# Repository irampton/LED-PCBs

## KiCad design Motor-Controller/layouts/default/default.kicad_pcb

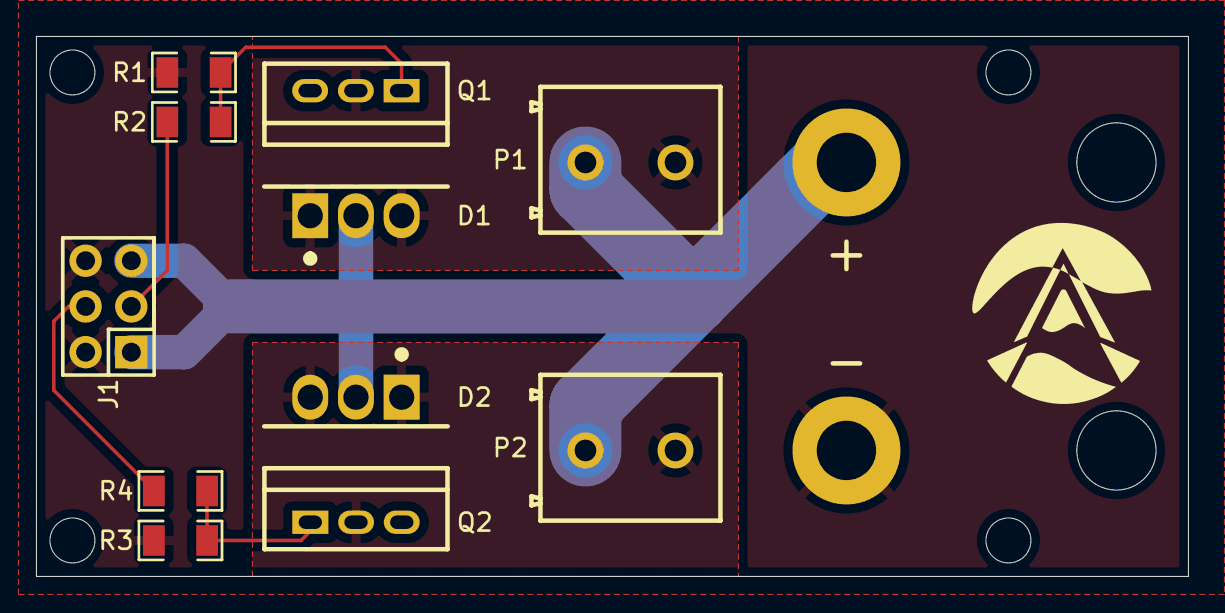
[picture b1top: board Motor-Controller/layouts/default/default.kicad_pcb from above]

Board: 2 copper layers, 64.0 x 30.0 mm, 13 parts (0 on the bottom side), 8 nets.

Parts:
+: M18_10AWG_PAD
-: M18_10AWG_PAD
D1, D2: TO-220AB-3_L10.4-W4.6-P2.54-T
J1: HDR-TH_6P-P2.54-V-M-R2-C3-S2.54-1
P1, P2: CONN-TH_2P-P5.00_CPC3703CTR
Q1, Q2: TO-220AB-3_L10.3-W4.5-P2.54-L-1
R1, R3: 10kΩ ±1%; R1206
R2, R4: 330Ω ±5%; R1206

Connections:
GATE1: Q1.1, R1.1, R2.2
GATE2: Q2.1, R3.1, R4.2
MOTOR1: D1.1, D1.3, P1.2, Q1.2
MOTOR2: D2.1, D2.3, P2.2, Q2.2
PWM1: J1.3, R2.1
PWM2: J1.4, R4.1
hv: +.1, D1.2, D2.2, J1.1, J1.5, P1.1, P2.1
lv: -.1, J1.2, J1.6, Q1.3, Q2.3, R1.2, R3.2

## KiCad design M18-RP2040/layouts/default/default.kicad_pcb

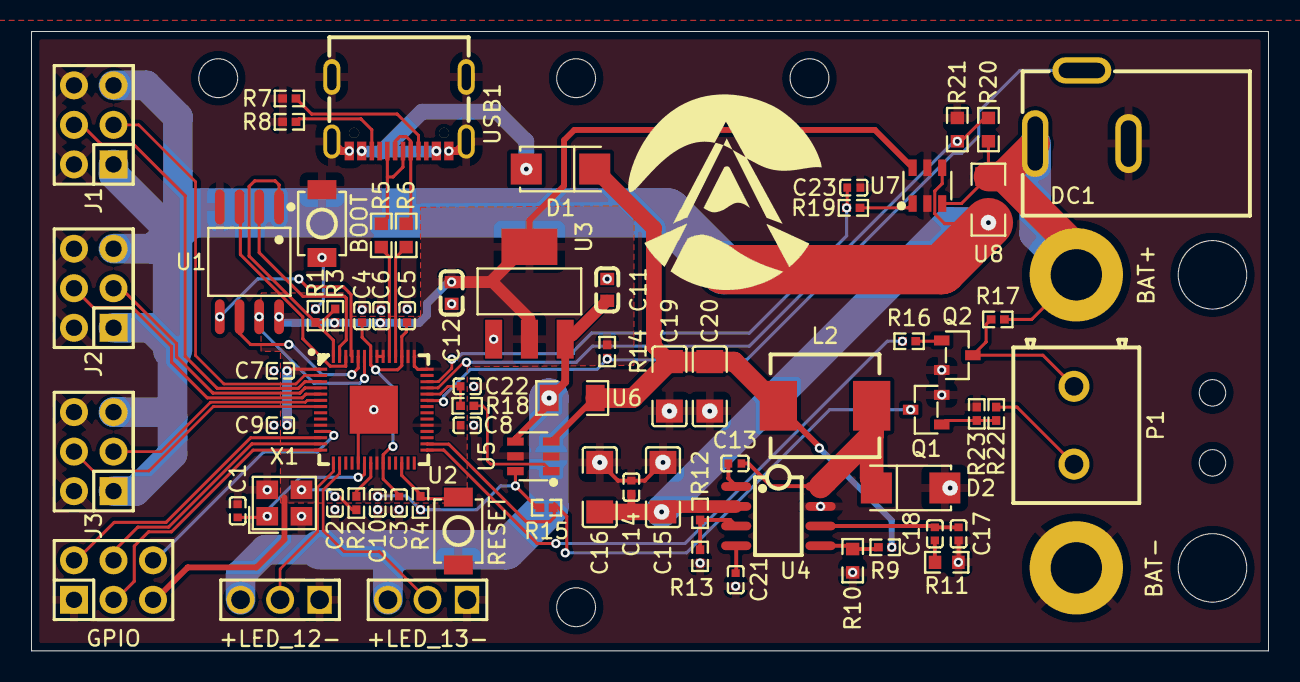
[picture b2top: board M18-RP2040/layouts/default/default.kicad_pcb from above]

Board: 2 copper layers, 79.5 x 39.8 mm, 73 parts (0 on the bottom side), 56 nets.

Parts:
+LED_12-, +LED_13-: HDR-TH_3P-P2.54-V-M-1
BAT+: M18_10AWG_PAD
BAT-: M18_10AWG_PAD
BOOT: SW-SMD_L3.9-W3.0-P4.45
C1, C2: 22pF ±5%; C0402
C3, C4, C5, C6, C7, C8, C9, C10: 1µF ±10%; C0402
C11: 10µF ±10%; C0603
C12: 22µF ±20%; C0603
C13: 100nF ±10%; C0402
C14, C21, C22, C23: 10nF ±10%; C0402
C15, C16: 4.7µF ±10%; C1206
C17: 47pF ±5%; C0402
C18: 1nF ±10%; C0402
C19, C20: 47µF ±20%; C1206
D1: SMA_L4.3-W2.6-LS5.2-RD
D2: Vf {ℝ+}V; SMA_L4.3-W2.6-LS5.2-RD
DC1: DC-IN-TH_PJ-002BH
GPIO: HDR-TH_6P-P2.54-V-M-R2-C3-S2.54-1
J1, J2, J3: HDR-TH_6P-P2.54-V-M-R2-C3-S2.54-1
L2: L 6.8µH ±20%; IND-SMD_L7.0-W6.6
P1: CONN-TH_2P-P5.00_CPC3703CTR
Q1, Q2: SOT-23-3_L2.9-W1.3-P1.90-LS2.4-BR
R1, R2: 1kΩ ±1%; R0402
R3, R4, R9, R14, R15, R17, R22, R23: 10kΩ ±1%; R0402
R5, R6: 22Ω ±1%; R0603
R7, R8: 5.1kΩ ±1%; R0402
R10: 1.8kΩ ±1%; R0603
R11: 30kΩ ±1%; R0603
R12: 330kΩ ±1%; R0402
R13: 68kΩ ±1%; R0402
R16: 330Ω ±1%; R0402
R18, R19: 220Ω ±1%; R0402
R20: 150kΩ ±1%; R0603
R21: 22kΩ ±1%; R0603
RESET: SW-SMD_L3.9-W3.0-P4.45
U1: SOIC-8_L5.3-W5.3-P1.27-LS8.0-BL
U2: LQFN-56_L7.0-W7.0-P0.4-EP
U3: SOT-223-3_L6.5-W3.4-P2.30-LS7.0-BR
U4: SOIC-8_L5.0-W4.0-P1.27-LS6.0-BL
U5, U7: SOT-23-6_L2.9-W1.6-P0.95-LS2.8-BL
U6, U8: R1206
USB1: USB-C_UC09-0B16F00P11
X1: CRYSTAL-SMD_4P-L3.2-W2.5-BL

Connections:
1V1: C3.1, C4.1, C5.1, U2.23, U2.45, U2.50
3: DC1.3, R14.1, U2.37
3V3: C6.1, C7.1, C8.1, C9.1, C10.1, C12.1, GPIO.5, R3.1, R4.1, R14.2, R15.1, U1.8, U2.1, U2.10, U2.22, U2.33, U2.42, U2.43, U2.44, U2.48, U2.49, U3.2, U3.4, U5.6, U7.6
5V: +LED_12-.3, +LED_13-.3, C11.1, U3.3, U5.4, U6.2
5Vin: C19.1, C20.1, D1.1, L2.2, R9.1, U5.3, U6.1
CC1: R7.1, USB1.A5
CC2: R8.1, USB1.B5
D: Q1.3, R15.2, U2.30
DATA_N: R6.1, USB1.A7, USB1.B7
DATA_P: R5.1, USB1.A6, USB1.B6
DC: P1.2, R22.1
DP: P1.1, Q2.3, R17.2
EN: R12.2, R13.1, U4.3
G: Q1.1, R22.2, R23.1
G-1: Q2.1, R16.1
GND: +LED_12-.1, +LED_13-.1, BAT-.1, BOOT.1, C1.2, C2.2, C3.2, C4.2, C5.2, C6.2, C7.2, C8.2, C9.2, C10.2, C11.2, C12.2, C14.2, C15.2, C16.2, C17.2, C19.2, C20.2, C21.2, C22.2, C23.2, D2.2, DC1.2, GPIO.1, J1.2, J1.6, J2.2, J2.6, J3.2, J3.6, Q1.2, Q2.2, R7.2, R8.2, R10.2, R11.2, R13.2, R21.2, R23.2, RESET.1, U1.4, U2.19, U2.57, U3.1, U4.7, U5.2, U5.5, U7.2, U7.5, USB1.17, USB1.18, USB1.19, USB1.20, USB1.A1B12, USB1.B1A12, X1.2, X1.4
GPIO0: J1.3, U2.2
GPIO1: J1.4, U2.3
GPIO2: J2.3, U2.4
GPIO3: J2.4, U2.5
GPIO4: J3.3, U2.6
GPIO5: J3.4, U2.7
GPIO12: +LED_12-.2, U2.15
GPIO13: +LED_13-.2, U2.16
MISO: GPIO.6, U2.11
MOSI: GPIO.3, U2.14
OUT: R18.1, U5.1
OUT-1: R19.1, U7.1
RUN: R4.2, RESET.2, U2.26
SCLK: GPIO.4, U2.13
USB_DM: R6.2, U2.46
USB_DP: R5.2, U2.47
V+: C14.1, C15.1, C16.1, J1.1, J1.5, J2.1, J2.5, J3.1, J3.5, R12.1, U4.2, U7.4, U8.2
VIN: BAT+.1, DC1.1, R17.1, R20.1, U7.3, U8.1
VSENSE: R9.2, R10.1, U4.5
XOUT: R2.1, U2.21
boot_cap-power-hv: C13.1, U4.1
c_osc_1-power-hv: C1.1, U2.20, X1.1
c_osc_2-power-hv: C2.1, R2.2, X1.3
cathode: C13.2, D2.1, L2.1, U4.8
comp_c2-power-hv: C17.1, C18.1, U4.6
cs: R1.2, R3.2, U1.1, U2.56
gpio18: R16.2, U2.29
gpio27_a1: R20.2, R21.1, U2.39
hv: C22.1, R18.2, U2.38
io0: U1.5, U2.53
io1: U1.2, U2.55
io2: U1.3, U2.54
io3: U1.7, U2.51
lv: C18.2, R11.1
output: BOOT.2, R1.1
sclk: U1.6, U2.52
spi_cs: GPIO.2, U2.12
ss_cap-power-hv: C21.1, U4.4
vUSB: D1.2, USB1.A4B9, USB1.B4A9
vin_sense_c1-power-hv: C23.1, R19.2, U2.40

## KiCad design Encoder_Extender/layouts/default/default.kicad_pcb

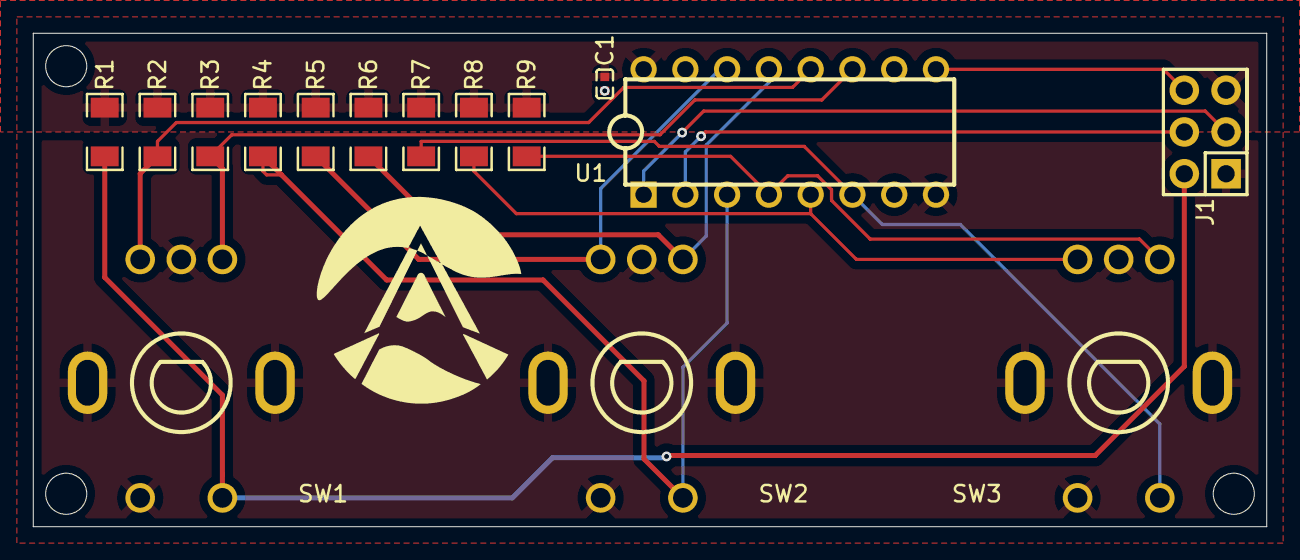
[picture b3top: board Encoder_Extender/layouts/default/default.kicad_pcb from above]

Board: 2 copper layers, 75.0 x 30.0 mm, 16 parts (1 on the bottom side), 14 nets.

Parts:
C1: 100nF ±10%; C0402
J1: HDR-TH_6P-P2.54-V-M-R2-C3-S2.54-1
QR*****: LED-GitHub-QR-MD
R1, R2, R3, R4, R5, R6, R7, R8, R9: 10kΩ ±1%; R1206
SW1, SW2, SW3: SW-TH_5P-L12.5-W13.4-P2.50-LS14.5
U1: DIP-16_L19.8-W6.5-P2.54-LS7.6-BL

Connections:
3V3: C1.1, J1.5, R1.1, R2.1, R3.1, R4.1, R5.1, R6.1, R7.1, R8.1, R9.1, U1.16
A: R3.2, SW1.1, U1.11
A-1: R6.2, SW2.1, U1.13
A-2: R9.2, SW3.1, U1.4
B: R2.2, SW1.3, U1.12
B-1: R5.2, SW2.3, U1.14
B-2: R8.2, SW3.3, U1.5
CLOCK: J1.4, U1.2
CS: J1.2, R1.2, SW1.4
E: R4.2, SW2.4, U1.3
GND: C1.2, J1.1, SW1.2, SW1.5, SW1.7, SW1.8, SW2.2, SW2.5, SW2.7, SW2.8, SW3.2, SW3.5, SW3.7, SW3.8, U1.8, U1.10, U1.15
H: R7.2, SW3.4, U1.6
RX: J1.6, U1.9
TX: J1.3, U1.1

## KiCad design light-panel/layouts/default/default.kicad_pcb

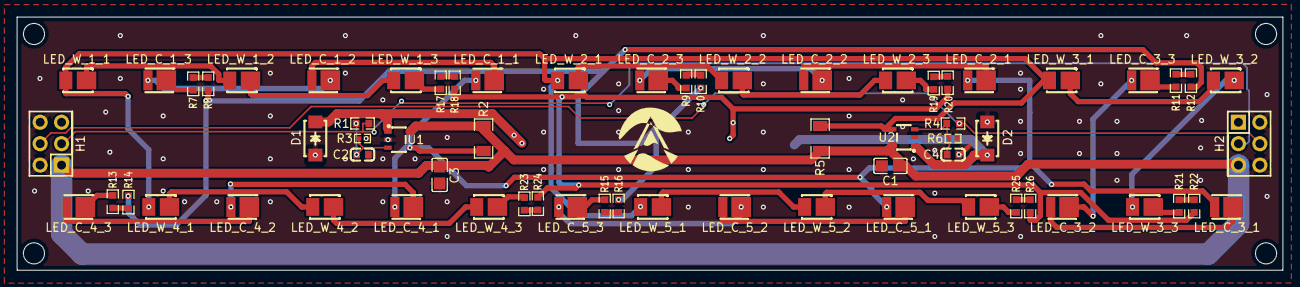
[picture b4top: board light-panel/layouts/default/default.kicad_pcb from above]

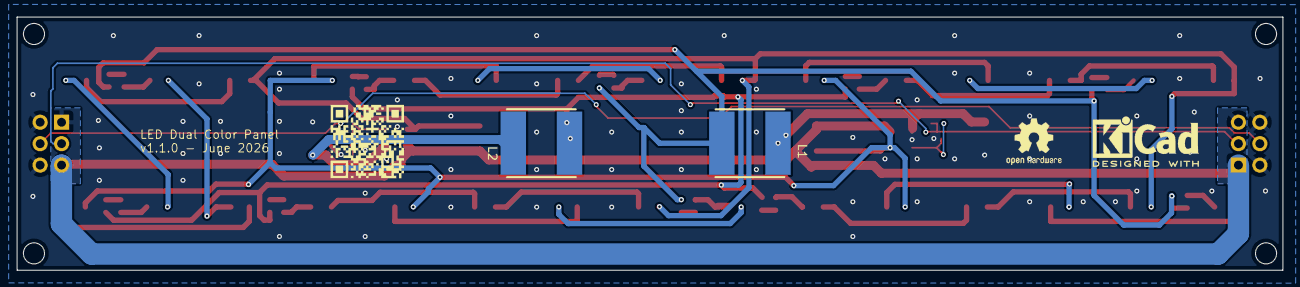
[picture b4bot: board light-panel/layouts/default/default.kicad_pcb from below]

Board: 2 copper layers, 150.0 x 30.0 mm, 69 parts (3 on the bottom side), 52 nets.

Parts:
C1, C3: 10µF ±10%; C0805
C2, C4: 100nF ±10%; C0603
D1, D2: SMA_L4.2-W2.6-LS5.0-RD_1
H1, H2: HDR-TH_6P-P2.54-V-M-R2-C3-S2.54-1
L1, L2: L 68µH ±20%; IND-SMD_L8.0-W8.0
LED_C_1_1, LED_C_1_2, LED_C_1_3, LED_C_2_1, LED_C_2_2, LED_C_2_3, LED_C_3_1, LED_C_3_2, LED_C_3_3, LED_C_4_1, LED_C_4_2, LED_C_4_3, LED_C_5_1, LED_C_5_2, LED_C_5_3: LED-SMD_L3.3-W2.8-RD
LED_W_1_1, LED_W_1_2, LED_W_1_3, LED_W_2_1, LED_W_2_2, LED_W_2_3, LED_W_3_1, LED_W_3_2, LED_W_3_3, LED_W_4_1, LED_W_4_2, LED_W_4_3, LED_W_5_1, LED_W_5_2, LED_W_5_3: LED-SMD_L3.5-W2.8-FD-2835_WHITE
QR*****: LED-GitHub-QR-MD
R1, R4: 6.8kΩ ±1%; R0603
R2, R5: 170mΩ ±1%; R1206
R3, R6: 22kΩ ±1%; R0402
R7, R8, R9, R10, R11, R12, R13, R14, R15, R16, R17, R18, R19, R20, R21, R22, R23, R24, R25, R26: R0603
U1, U2: TSOT-25_L2.9-W1.6-P0.95-LS2.8-BR

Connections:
1: LED_C_1_3.1, R7.1
2: L1.1, R8.2, R10.2, R12.2, R14.2, R16.2
A: LED_C_1_1.2, LED_C_2_1.2, LED_C_3_1.2, LED_C_4_1.2, LED_C_5_1.2, R2.2, U1.4
GND: C1.2, C2.2, C3.2, C4.2, D1.2, D2.2, H1.2, H1.6, H2.2, H2.6, R3.2, R6.2, U1.2, U2.2
V+: C1.1, C3.1, H1.1, H1.5, H2.1, H2.5, R2.1, R5.1, U1.5, U2.5
cool_led-1: R7.2, R8.1
cool_led-1-1: LED_C_2_3.1, R9.1
cool_led-1-2: R9.2, R10.1
cool_led-1-3: LED_C_3_3.1, R11.1
cool_led-1-4: R11.2, R12.1
cool_led-1-5: LED_C_4_3.1, R13.1
cool_led-1-6: R13.2, R14.1
cool_led-1-7: LED_C_5_3.1, R15.1
cool_led-1-8: R15.2, R16.1
cool_led-A: LED_C_1_1.1, LED_C_1_2.2
cool_led-A-1: LED_C_4_2.1, LED_C_4_3.2
cool_led-A-2: LED_C_4_1.1, LED_C_4_2.2
cool_led-A-3: LED_C_5_1.1, LED_C_5_2.2
cool_led-A-4: LED_C_5_2.1, LED_C_5_3.2
cool_led-A-5: LED_C_1_2.1, LED_C_1_3.2
cool_led-A-6: LED_C_2_1.1, LED_C_2_2.2
cool_led-A-7: LED_C_2_2.1, LED_C_2_3.2
cool_led-A-8: LED_C_3_1.1, LED_C_3_2.2
cool_led-A-9: LED_C_3_2.1, LED_C_3_3.2
cool_led.channel-1: D1.1, L1.2, U1.1
hv: C2.1, R1.2, R3.1, U1.3
pwm_cool: H1.3, H2.3, R1.1
pwm_warm: H1.4, H2.4, R4.1
vset_filter_cap-power-hv: C4.1, R4.2, R6.1, U2.3
warm_led-1: LED_W_1_3.1, R17.1
warm_led-1-1: R17.2, R18.1
warm_led-1-2: LED_W_2_3.1, R19.1
warm_led-1-3: R19.2, R20.1
warm_led-1-4: LED_W_3_3.1, R21.1
warm_led-1-5: R21.2, R22.1
warm_led-1-6: LED_W_4_3.1, R23.1
warm_led-1-7: R23.2, R24.1
warm_led-1-8: LED_W_5_3.1, R25.1
warm_led-1-9: R25.2, R26.1
warm_led-2: L2.1, R18.2, R20.2, R22.2, R24.2, R26.2
warm_led-A: LED_W_1_1.2, LED_W_2_1.2, LED_W_3_1.2, LED_W_4_1.2, LED_W_5_1.2, R5.2, U2.4
warm_led-A-1: LED_W_1_1.1, LED_W_1_2.2
warm_led-A-2: LED_W_4_2.1, LED_W_4_3.2
warm_led-A-3: LED_W_4_1.1, LED_W_4_2.2
warm_led-A-4: LED_W_5_1.1, LED_W_5_2.2
warm_led-A-5: LED_W_5_2.1, LED_W_5_3.2
warm_led-A-6: LED_W_1_2.1, LED_W_1_3.2
warm_led-A-7: LED_W_2_1.1, LED_W_2_2.2
warm_led-A-8: LED_W_2_2.1, LED_W_2_3.2
warm_led-A-9: LED_W_3_1.1, LED_W_3_2.2
warm_led-A-10: LED_W_3_2.1, LED_W_3_3.2
warm_led.channel-1: D2.1, L2.2, U2.1

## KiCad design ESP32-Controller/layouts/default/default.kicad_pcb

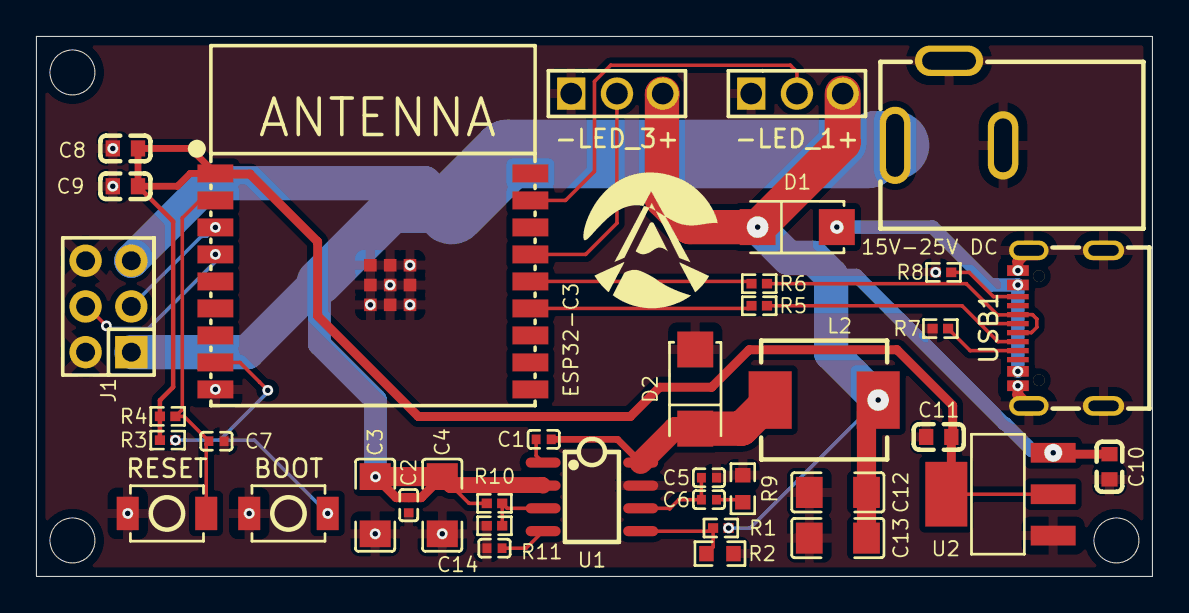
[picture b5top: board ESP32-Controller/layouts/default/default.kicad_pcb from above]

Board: 2 copper layers, 62.0 x 30.0 mm, 39 parts (1 on the bottom side), 24 nets.

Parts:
15V-25V DC: DC-IN-TH_PJ-002BH
-LED_1+, -LED_3+: HDR-TH_3P-P2.54-V-M-1
BOOT: SW-SMD_L3.9-W3.0-P4.45
C1: 100nF ±10%; C0402
C2, C14: 10nF ±10%; C0402
C3, C4: 4.7µF ±20%; C1206
C5: 47pF ±5%; C0402
C6: 1nF ±10%; C0402
C7: 1µF ±20%; C0402
C8, C10: 10µF ±20%; C0603
C9: 100nF ±20%; C0603
C11: 22µF ±20%; C0603
C12, C13: 47µF ±20%; C1206
D1: SMA_L4.3-W2.6-LS5.2-RD
D2: Vf {ℝ+}V; SMA_L4.3-W2.6-LS5.2-RD
ESP32-C3: BULETM-SMD_ESPRESSIF_ESP32-C3-WROOM-02-N4-4MB
J1: HDR-TH_6P-P2.54-V-M-R2-C3-S2.54-1
L2: L 6.8µH ±20%; IND-SMD_L7.0-W6.6
QR*****: LED-GitHub-QR-MD
R1: {ℝ+}Ω; R0402
R2: {ℝ+}Ω; R0603
R3, R4: 10kΩ ±5%; R0402
R5, R6: 22Ω ±5%; R0402
R7, R8: 5.1kΩ ±5%; R0402
R9: 30kΩ ±1%; R0603
R10: 330kΩ ±1%; R0402
R11: 68kΩ ±1%; R0402
RESET: SW-SMD_L3.9-W3.0-P4.45
U1: SOIC-8_L5.0-W4.0-P1.27-LS6.0-BL
U2: SOT-223-3_L6.5-W3.4-P2.30-LS7.0-BR
USB1: USB-C_UC09-0B16F00P11

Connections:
2: -LED_1+.2, ESP32-C3.17
2-1: -LED_3+.2, ESP32-C3.15
3V3: C8.1, C9.1, C11.1, ESP32-C3.1, R3.1, R4.1, U2.2, U2.4
5V: -LED_1+.3, -LED_3+.3, C10.1, C12.1, C13.1, D1.1, L2.2, R1.1, U2.3
13: ESP32-C3.13, R5.2
14: ESP32-C3.14, R6.2
BOOT: BOOT.1, ESP32-C3.8, R3.2
CC1: R7.1, USB1.A5
CC2: R8.1, USB1.B5
EN: R10.2, R11.1, U1.3
GND: 15V-25V DC.2, 15V-25V DC.3, -LED_1+.1, -LED_3+.1, BOOT.2, C2.2, C3.2, C4.2, C5.2, C7.2, C8.2, C9.2, C10.2, C11.2, C12.2, C13.2, C14.2, D2.2, ESP32-C3.9, ESP32-C3.19, J1.2, J1.6, R2.2, R7.2, R8.2, R9.2, R11.2, RESET.2, U1.7, U2.1, USB1.17, USB1.18, USB1.19, USB1.20, USB1.A1B12, USB1.B1A12
RESET: C7.1, ESP32-C3.2, R4.2, RESET.1
V+: 15V-25V DC.1, C2.1, C3.1, C4.1, J1.1, J1.5, R10.1, U1.2
VSENSE: R1.2, R2.1, U1.5
cathode: C1.2, D2.1, L2.1, U1.8
comp_c2-power-hv: C5.1, C6.1, U1.6
hv: C1.1, U1.1
lv: C6.2, R9.1
pwm_cool: ESP32-C3.3, J1.3
pwm_warm: ESP32-C3.4, J1.4
ss_cap-power-hv: C14.1, U1.4
usb_n: R5.1, USB1.A7, USB1.B7
usb_p: R6.1, USB1.A6, USB1.B6
vUSB: D1.2, USB1.A4B9, USB1.B4A9

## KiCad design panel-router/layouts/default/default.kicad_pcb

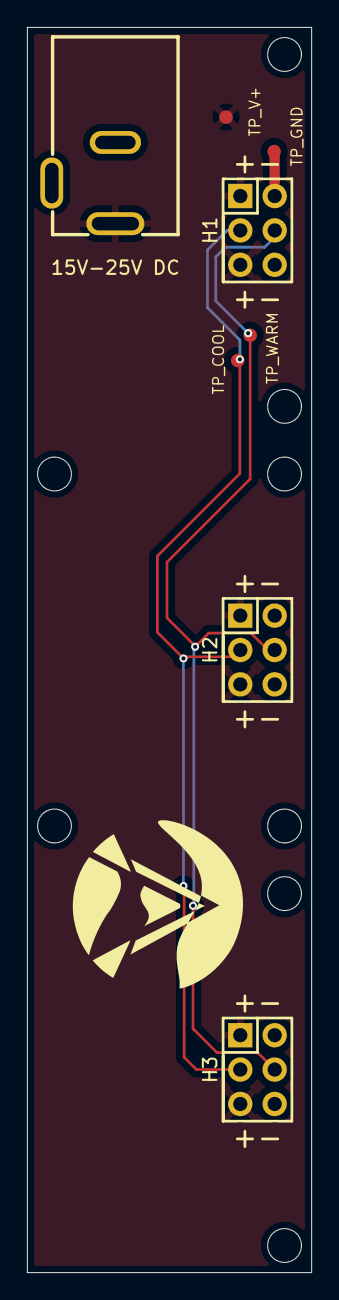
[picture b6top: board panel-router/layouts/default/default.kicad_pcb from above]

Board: 2 copper layers, 21.0 x 92.0 mm, 9 parts (1 on the bottom side), 4 nets.

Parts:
15V-25V DC: DC-IN-TH_PJ-002BH
H1, H2, H3: HDR-TH_6P-P2.54-V-M-R2-C3-S2.54-1
QR*****: LED-GitHub-QR-MD
TP_COOL: TestPoint_Pad_D1.0mm
TP_GND: TestPoint_Pad_D1.0mm
TP_V+: TestPoint_Pad_D1.0mm
TP_WARM: TestPoint_Pad_D1.0mm

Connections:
3: H1.3, H2.3, H3.3, TP_COOL.1
4: H1.4, H2.4, H3.4, TP_WARM.1
GND: 15V-25V DC.2, 15V-25V DC.3, H1.2, H1.6, H2.2, H2.6, H3.2, H3.6, TP_GND.1
V+: 15V-25V DC.1, H1.1, H1.5, H2.1, H2.5, H3.1, H3.5, TP_V+.1

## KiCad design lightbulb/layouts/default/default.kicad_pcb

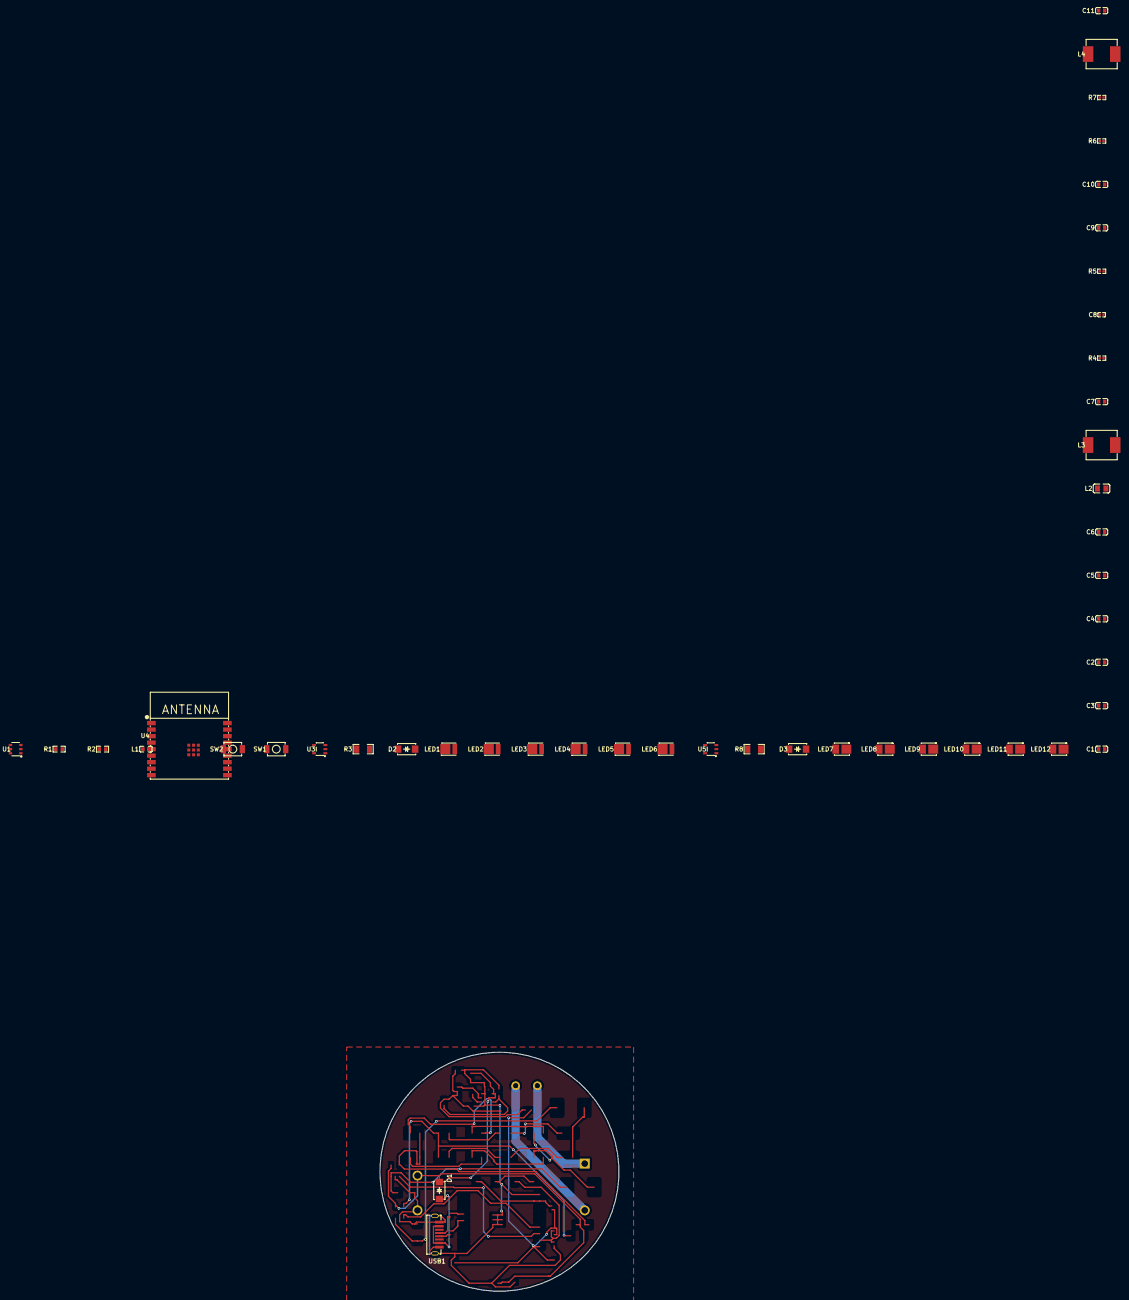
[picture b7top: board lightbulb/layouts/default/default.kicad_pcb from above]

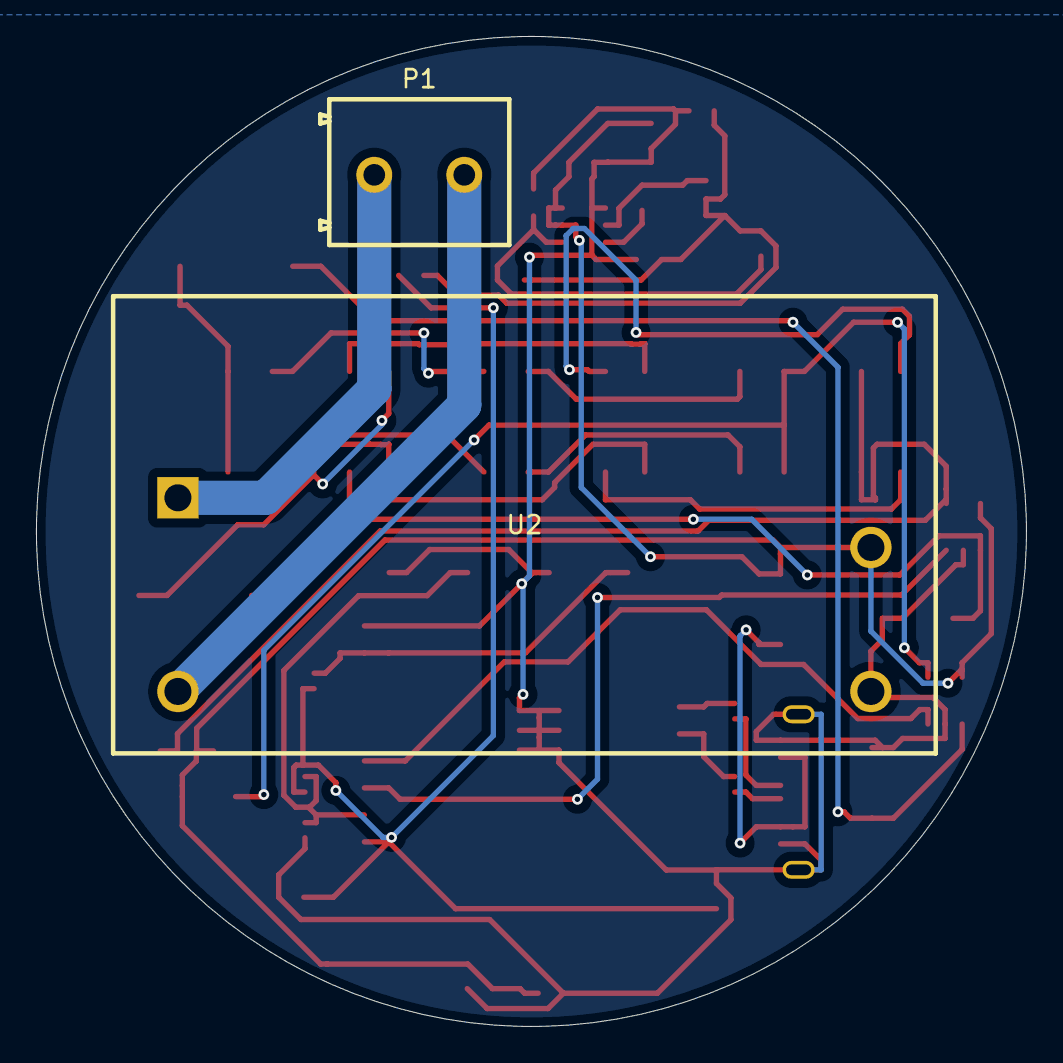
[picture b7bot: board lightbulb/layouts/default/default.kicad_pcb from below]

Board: 2 copper layers, 55.0 x 55.0 mm, 47 parts (2 on the bottom side), 32 nets.

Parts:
C1, C2, C10: 100nF ±10%; C0603
C3, C7, C9, C11: 10µF ±10%; C0603
C4, C5: 22µF ±20%; C0603
C6: 47pF ±5%; C0603
C8: 1µF ±10%; C0402
D1, D2, D3: SMA_L4.2-W2.6-LS5.0-RD_1
L1: L0603
L2: L 6.8µH ±20%; L0805
L3, L4: L 47µH ±20%; IND-SMD_L7.0-W6.6_FXL0630
LED1, LED2, LED3, LED4, LED5, LED6: LED-SMD_L3.3-W2.8-RD
LED7, LED8, LED9, LED10, LED11, LED12: LED-SMD_L3.5-W2.8-FD-2835_WHITE
P1: CONN-TH_2P-P5.00_CPC3703CTR
R1, R2: R0603
R3, R8: R1206
R4, R5: 10kΩ ±1%; R0402
R6, R7: 22Ω ±1%; R0402
SW1, SW2: SW-SMD_L3.9-W3.0-P4.45
U1: TSOT-23-6_L2.9-W1.6-P0.95-LS2.8-BR
U2: PWRM-TH_IRM-10-12
U3, U5: TSOT-25_L2.9-W1.6-P0.95-LS2.8-BR
U4: BULETM-SMD_ESPRESSIF_ESP32-C3-WROOM-02-N4-4MB
USB1: USB-C-SMD_MC-401L68-Z09

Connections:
1: P1.1, U2.1
2: P1.2, U2.2
3: U3.3, U4.3
13: R6.2, U4.13
14: R7.2, U4.14
A: LED1.2, LED4.2, R3.2, U3.4
A6: R7.1, USB1.A6
A7: R6.1, USB1.A7
A-1: D1.2, USB1.B4, USB1.B9
C: L3.1, LED3.1, LED6.1
K: L4.1, LED9.1, LED12.1
VSET: U4.4, U5.3
bst_cap-power-hv: C1.1, U1.6
cool_led-A: LED1.1, LED2.2
cool_led-A-1: LED2.1, LED3.2
cool_led-A-2: LED4.1, LED5.2
cool_led-A-3: LED5.1, LED6.2
cool_led.channel-1: D2.1, L3.2, U3.1
en_cap-power-hv: C8.1, R5.2, SW2.1, U4.2
esp32-A: R4.2, SW1.1, U4.8
esp32_bypass_cap-power-hv: C9.1, C10.1, L1.2, R4.1, R5.1, U4.1
fb_cap-power-lv: C6.2, R1.2, R2.1, U1.1
hv: C4.1, C5.1, C6.1, L1.1, L2.2, R1.1
input_cap-power-hv: C2.1, C3.1, C7.1, C11.1, D1.1, R3.1, R8.1, U1.2, U1.3, U2.4, U3.5, U5.5
input_cap-power-lv: C2.2, C3.2, C4.2, C5.2, C7.2, C8.2, C9.2, C10.2, C11.2, D2.2, D3.2, R2.2, SW1.2, SW2.2, U1.4, U2.3, U3.2, U4.9, U4.19, U5.2, USB1.9, USB1.10, USB1.B1, USB1.B12
lv: C1.2, L2.1, U1.5
warm_led-A: LED7.2, LED10.2, R8.2, U5.4
warm_led-A-1: LED7.1, LED8.2
warm_led-A-2: LED8.1, LED9.2
warm_led-A-3: LED10.1, LED11.2
warm_led-A-4: LED11.1, LED12.2
warm_led.channel-1: D3.1, L4.2, U5.1

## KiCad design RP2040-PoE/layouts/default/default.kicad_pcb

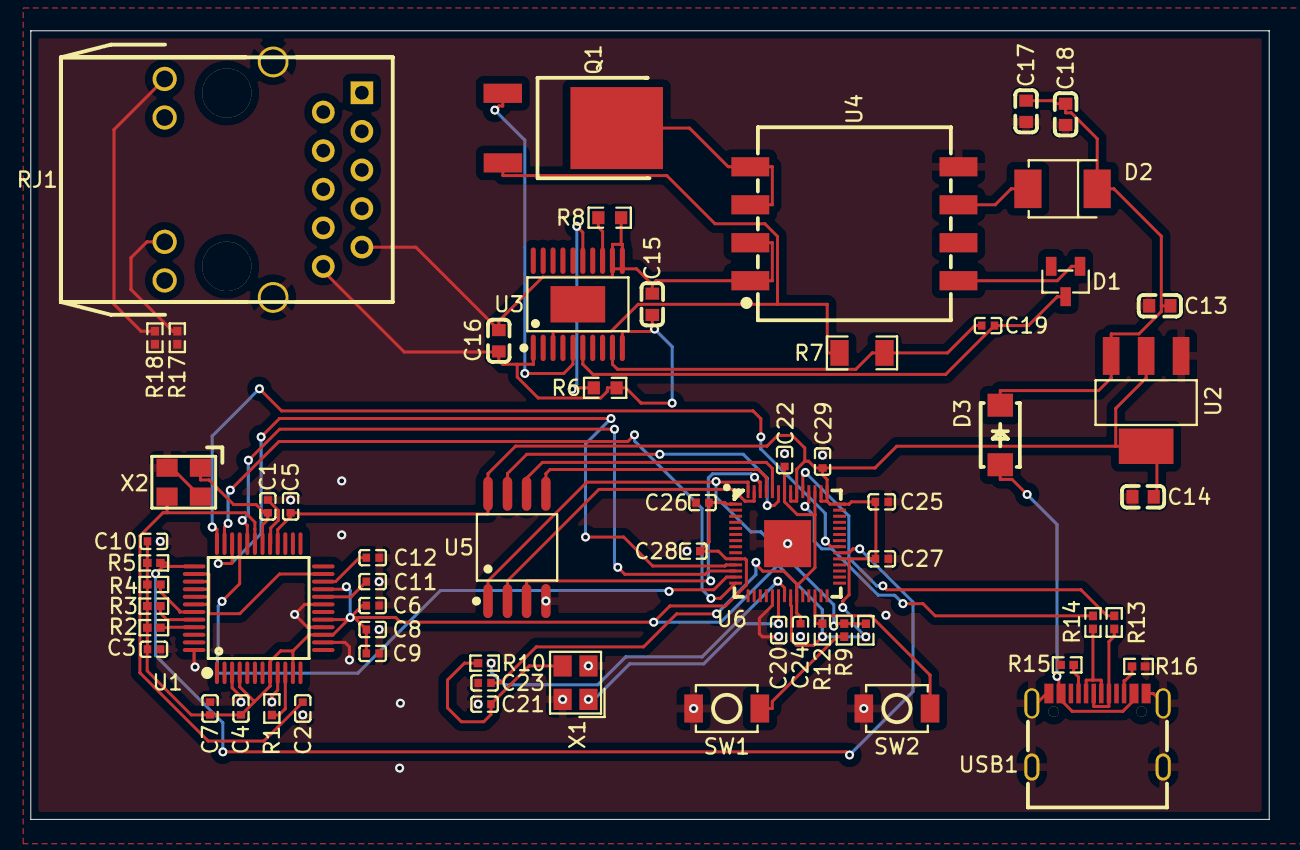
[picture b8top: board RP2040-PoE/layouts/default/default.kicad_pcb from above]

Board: 2 copper layers, 81.5 x 51.9 mm, 63 parts (0 on the bottom side), 56 nets.

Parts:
C1, C2: 18pF ±5%; C0402
C3, C4, C5, C6, C7, C8, C9, C10: 100nF ±10%; C0402
C11: 2.2µF ±20%; C0402
C12, C19, C22, C23, C24, C25, C26, C27, C28, C29: 1µF ±10%; C0402
C13, C15: 10µF ±10%; C0603
C14, C17, C18: 22µF ±20%; C0603
C16: 100nF ±10%; C0603
C20, C21: 22pF ±5%; C0402
D1: SOT-23-3_L2.9-W1.3-P1.90-LS2.4-BL-1
D2: SMBF_L4.3-W3.6-LS5.3-RD
D3: SMA_L4.2-W2.6-LS5.0-RD_1
Q1: TO-252-3_L6.5-W5.8-P4.58-BL
R1: 12.4kΩ ±1%; R0402
R2, R3, R4, R5, R11, R12: 10kΩ ±1%; R0402
R6: 63.4Ω ±1%; R0603
R7: 250mΩ ±1%; R1206
R8: 24.9kΩ ±1%; R0603
R9, R10: 1kΩ ±1%; R0402
R13, R14: 27Ω ±1%; R0402
R15, R16: 5.1kΩ ±1%; R0402
R17, R18: 270Ω ±1%; R0402
RJ1: RJ45-TH_HY931147C
SW1, SW2: SW-SMD_L3.9-W3.0-P4.45
U1: LQFP-48_L7.0-W7.0-P0.50-LS9.0-BL
U2: SOT-223-3_L6.5-W3.4-P2.30-LS7.0-BR
U3: HTSSOP-20_L6.5-W4.4-P0.65-LS6.4-BL-EP-1
U4: XFMR-SMD_HR051067
U5: SOIC-8_L5.3-W5.3-P1.27-LS8.0-BL
U6: LQFN-56_L7.0-W7.0-P0.4-EP
USB1: USB-C-SMD_KH-TYPE-C-16P
X1: CRYSTAL-SMD_4P-L3.2-W2.5-BL
X2: OSC-SMD_4P-L3.2-W2.5-BL_SIT8008BI

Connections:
3V3: C3.1, C4.1, C5.1, C6.1, C7.1, C8.1, C9.1, C10.1, C14.1, C25.1, C26.1, C27.1, C28.1, C29.1, R2.2, R3.2, R4.2, R5.1, R11.1, R12.1, R17.1, R18.1, U1.4, U1.8, U1.11, U1.15, U1.17, U1.21, U1.28, U2.2, U2.4, U5.8, U6.1, U6.10, U6.22, U6.33, U6.42, U6.43, U6.44, U6.48, U6.49
5V: C13.1, C17.1, C18.1, D2.1, D3.1, U2.3
10: R1.1, U1.10
43: R4.1, U1.43
44: R3.1, U1.44
45: R2.1, U1.45
A: D1.1, U4.8
A5: R15.1, USB1.A5
B5: R16.1, USB1.B5
CLS: R6.1, U3.15
D: Q1.2, U4.3, U4.4
DATA_N: R14.1, USB1.A7, USB1.B7
DATA_P: R13.1, USB1.A6, USB1.B6
DEN: R8.1, U3.13
G: Q1.1, U3.5
GND: C1.2, C2.2, C3.2, C4.2, C5.2, C6.2, C7.2, C8.2, C9.2, C10.2, C11.2, C12.2, C13.2, C14.2, C17.2, C18.2, C20.2, C21.2, C22.2, C23.2, C24.2, C25.2, C26.2, C27.2, C28.2, C29.2, R1.2, R15.2, R16.2, RJ1.GND1, RJ1.GND2, SW1.1, SW2.1, U1.3, U1.9, U1.14, U1.16, U1.19, U1.29, U1.48, U2.1, U4.5, U5.4, U6.19, U6.57, USB1.1, USB1.2, USB1.3, USB1.4, USB1.A1, USB1.A12, USB1.B1, USB1.B12, X1.2, X1.4, X2.2, X2.4
MISO: U1.34, U6.11
MOSI: U1.35, U6.14
RSVD: U1.23, U1.38, U1.39, U1.40, U1.41, U1.42
RUN: R12.2, SW2.2, U6.26
SCLK: U1.33, U6.13
USB_DM: R14.2, U6.46
USB_DP: R13.2, U6.47
XOUT: R10.1, U6.21
activity_led_anode: R18.2, RJ1.11
activity_led_cathode: RJ1.12, U1.27
c_osc_1-power-hv: C20.1, U6.20, X1.1
c_osc_2-power-hv: C21.1, R10.2, X1.3
clock_load_caps[1]-power-hv: C2.1, U1.31, X2.3
cs: U1.32, U6.12
current_sense_node: Q1.3, R7.1, U3.3
eth_int: U1.36, U6.35
green_led_anode: R17.2, RJ1.13
green_led_cathode: RJ1.14, U1.25
hv: C1.1, U1.30, X2.1
input_bypass-power-hv: C15.1, C16.1, R8.2, RJ1.9, U3.11, U3.12, U4.1, U4.2
io0: U5.5, U6.53
io1: U5.2, U6.55
io2: U5.3, U6.54
io3: U5.7, U6.51
lv: C15.2, C16.2, R6.2, RJ1.10, U3.1, U3.10
output: R9.1, SW1.2
phy_rx_n: RJ1.5, U1.5
phy_rx_p: RJ1.6, U1.6
phy_tx_n: RJ1.1, U1.1
phy_tx_p: RJ1.2, U1.2
poe-A: D2.2, U4.6
power_1V-hv: C22.1, C23.1, C24.1, U6.23, U6.45, U6.50
qspi-cs: R9.2, R11.2, U5.1, U6.56
rstn: R5.2, U1.37, U6.34
sclk: U5.6, U6.52
tocap-power-hv: C11.1, U1.20
usb-A: D3.2, USB1.A4, USB1.A9, USB1.B4, USB1.B9
v12_cap-power-hv: C12.1, U1.22
vc_hold-power-hv: C19.1, D1.3, U3.6
vc_hold-power-lv: C19.2, R7.2, U3.9

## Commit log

2026-05-06 initial commit of smart lightbulb v1
2026-05-06 First pass of leds
2026-05-06 v1 of flat panel
2026-05-06 minor panel improvements
2026-05-07 switched led inductors
2026-05-07 Panel Cleanup
2026-05-08 panel router
2026-05-08 Cleanup
2026-05-11 refactor dependencies
2026-05-11 Used basic buttons in RP2040 module
2026-05-11 PoE initial pass
2026-05-22 PoE Improvements
2026-05-22 Basic RP2040 Dev Board
2026-05-22 M18 Board Start
2026-05-24 M18 Buck Placement
2026-05-25 Updated Buck to TI for cost savings
2026-05-25 Basic Buck layout
2026-05-25 M18 Power In - First Pass
2026-05-27 Build clean up and buck routing
2026-05-28 Fixed contactor build errors
2026-05-29 ESP32 New Buck & Header Updates
2026-05-29 Header & Silkscreen Updates
2026-05-29 Fixed RP2040 board headers
2026-05-30 Fixed and routed M18 headers
2026-05-31 Basic layout tweaks
2026-06-01 Finishing up panel-router
2026-06-01 Updated LED Panel Headers
2026-06-02 Fixed 3D offsets, flipped some DC jacks, and added screw holes
2026-06-03 Fixed USB port
2026-06-05 Added Silkscreen for export
2026-06-05 First rotary PCB
2026-06-05 First pass on encoder board
2026-06-05 Added silkscreen
2026-06-05 Added DC resistor divider
2026-06-05 Re-added m18 rp2040 logos
2026-06-05 Motor controller board
